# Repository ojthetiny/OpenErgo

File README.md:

# OpenErgo
 Open Source Alice Keyboard

 Use as a base for your own designs, renders or order as is (read important info at the bottom).

Details:

   - Alice layout
   - Supports OG Alice plate
   - Chonky external weight
   - 7.5 degree typing angle.
   - Flush USB-C connector built into the PCB
   - Skuf feet.
   - 3 Piece construction for no external screws (aside from weight)

Important Info (READ BEFORE ORDERING):

   - I do not offer any sort of warranty for this, nor can I be held liable if something goes wrong.
   - Renders are not fully representative of the final product
   - Please, PLEASE look over the design before you do anything with it, it's possible and very likely that there are some errors, I'm just a human.
   - Theoretically universal Alice pcb support (bottom side USB), though the connector is possibly slightly misaligned, still untested

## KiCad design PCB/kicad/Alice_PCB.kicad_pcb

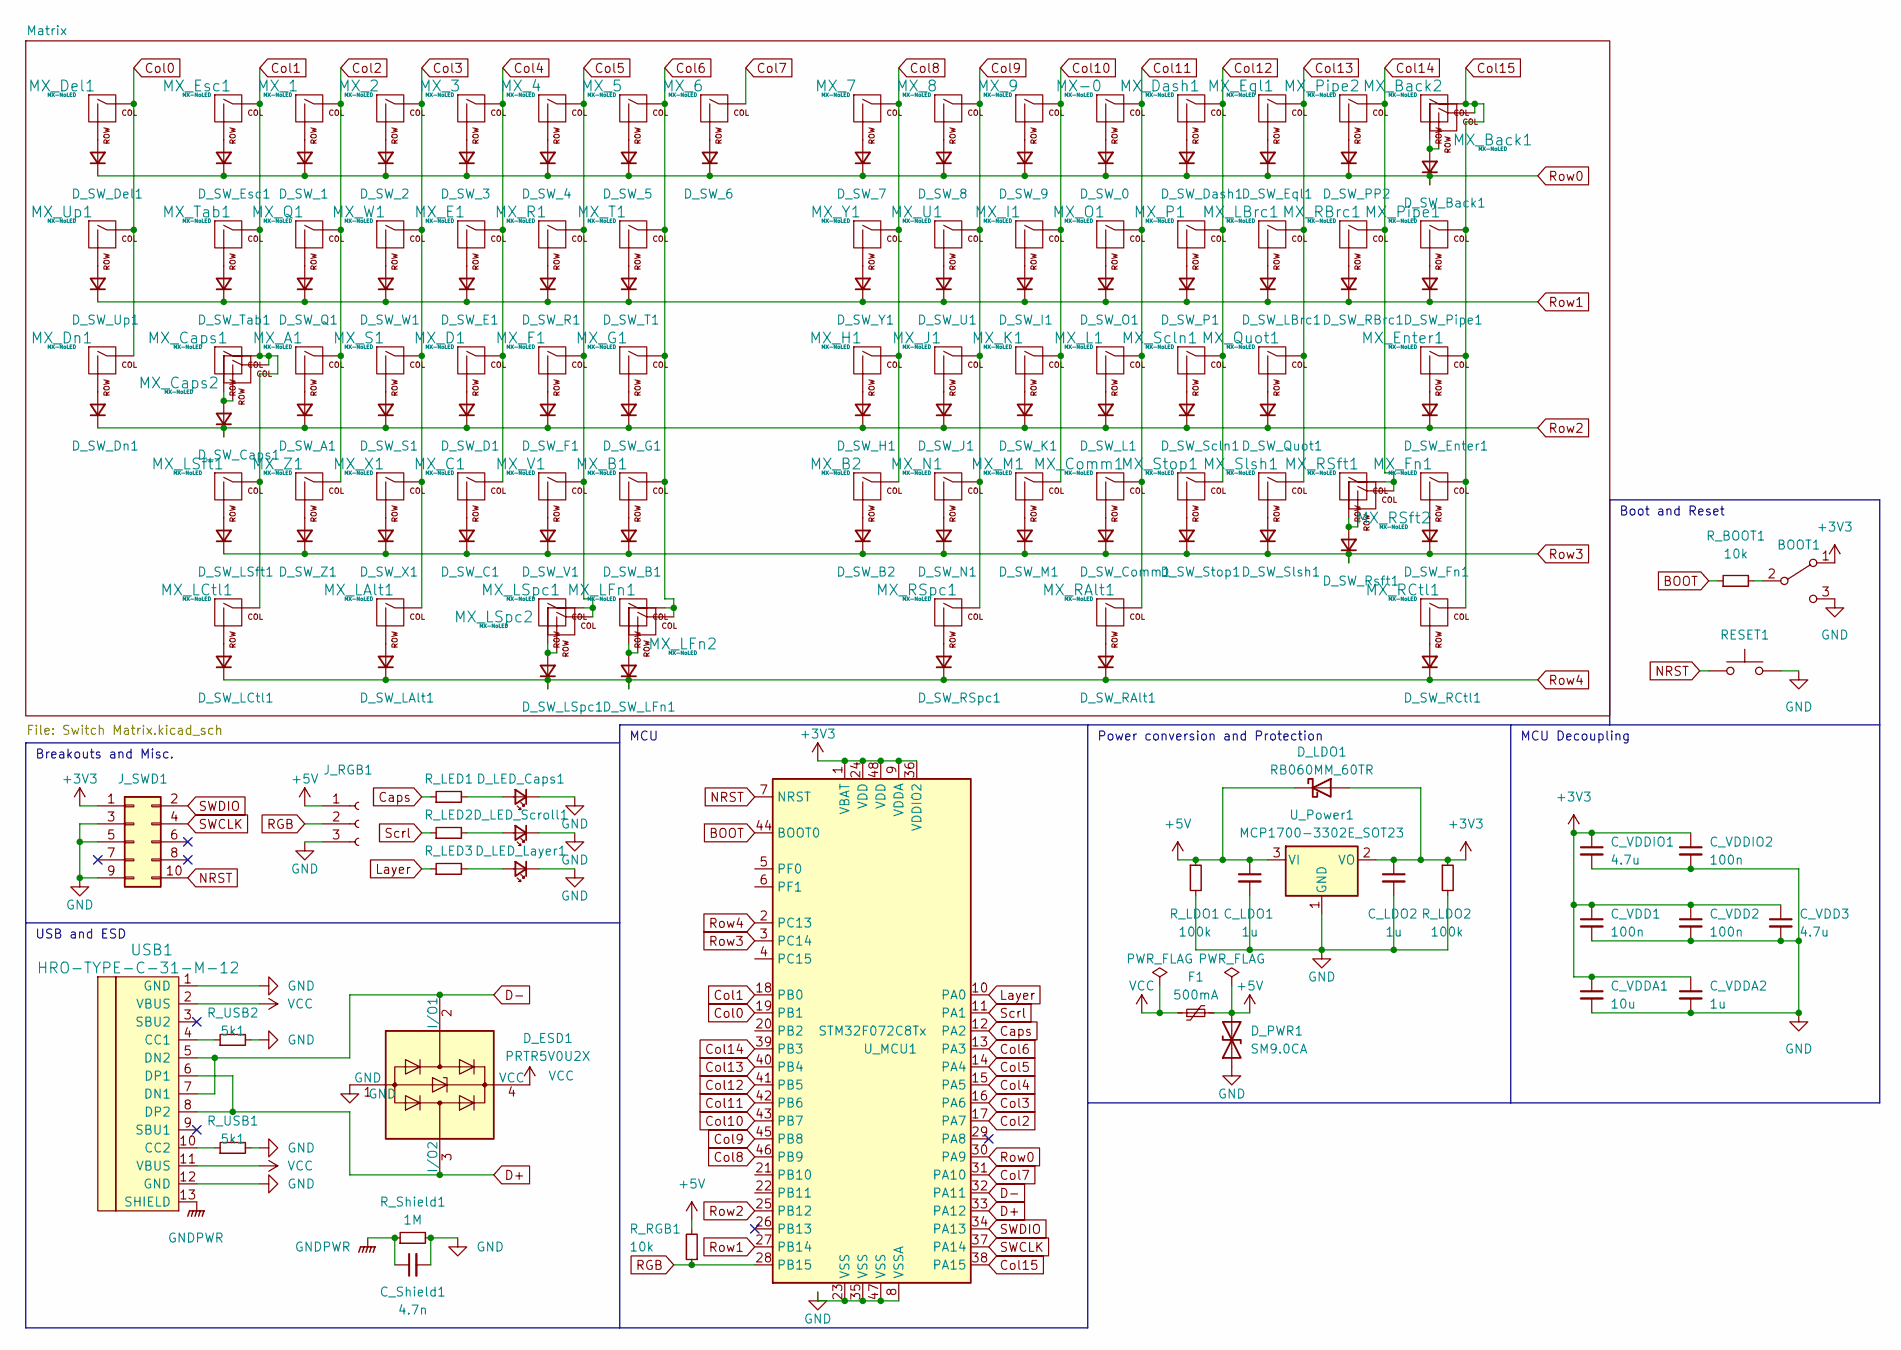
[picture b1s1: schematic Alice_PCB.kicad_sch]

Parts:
BOOT1: SW_SPDT; SW_SPDT_PCM12
C_LDO1, C_LDO2: 1u; C_0402_1005Metric
C_Shield1: 4.7n; C_0402_1005Metric
C_VDD1, C_VDD2: 100n; C_0402_1005Metric
C_VDD3: 4.7u; C_0402_1005Metric
C_VDDA1: 10u; C_0402_1005Metric
C_VDDA2: 1u; C_0402_1005Metric
C_VDDIO1: 4.7u; C_0402_1005Metric
C_VDDIO2: 100n; C_0402_1005Metric
D_ESD1: PRTR5V0U2X; SOT143B
D_LDO1: RB060MM_60TR; D_SOD-123
D_LED_Caps1: LED_Small; LED_3mm
D_LED_Layer1: LED_Small; LED_3mm
D_LED_Scroll1: LED_Small; LED_3mm
D_PWR1: SM9.0CA; D_SOD-123
D_SW_0, D_SW_1, D_SW_2, D_SW_3, D_SW_4, D_SW_5, D_SW_6, D_SW_7, D_SW_8, D_SW_9: D_Small; D_SOD-123
D_SW_A1: D_Small; D_SOD-123
D_SW_B1, D_SW_B2: D_Small; D_SOD-123
D_SW_Back1: D_Small; D_SOD-123
D_SW_C1: D_Small; D_SOD-123
D_SW_Caps1: D_Small; D_SOD-123
D_SW_Comm1: D_Small; D_SOD-123
D_SW_D1: D_Small; D_SOD-123
D_SW_Dash1: D_Small; D_SOD-123
D_SW_Del1: D_Small; D_SOD-123
D_SW_Dn1: D_Small; D_SOD-123
D_SW_E1: D_Small; D_SOD-123
D_SW_Enter1: D_Small; D_SOD-123
D_SW_Eql1: D_Small; D_SOD-123
D_SW_Esc1: D_Small; D_SOD-123
D_SW_F1: D_Small; D_SOD-123
D_SW_Fn1: D_Small; D_SOD-123
D_SW_G1: D_Small; D_SOD-123
D_SW_H1: D_Small; D_SOD-123
D_SW_I1: D_Small; D_SOD-123
D_SW_J1: D_Small; D_SOD-123
D_SW_K1: D_Small; D_SOD-123
D_SW_L1: D_Small; D_SOD-123
D_SW_LAlt1: D_Small; D_SOD-123
D_SW_LBrc1: D_Small; D_SOD-123
D_SW_LCtl1: D_Small; D_SOD-123
D_SW_LFn1: D_Small; D_SOD-123
D_SW_LSft1: D_Small; D_SOD-123
D_SW_LSpc1: D_Small; D_SOD-123
D_SW_M1: D_Small; D_SOD-123
D_SW_N1: D_Small; D_SOD-123
D_SW_O1: D_Small; D_SOD-123
D_SW_P1: D_Small; D_SOD-123
D_SW_PP2: D_Small; D_SOD-123
D_SW_Pipe1: D_Small; D_SOD-123
D_SW_Q1: D_Small; D_SOD-123
D_SW_Quot1: D_Small; D_SOD-123
D_SW_R1: D_Small; D_SOD-123
D_SW_RAlt1: D_Small; D_SOD-123
D_SW_RBrc1: D_Small; D_SOD-123
D_SW_RCtl1: D_Small; D_SOD-123
D_SW_RSpc1: D_Small; D_SOD-123
D_SW_Rsft1: D_Small; D_SOD-123
D_SW_S1: D_Small; D_SOD-123
D_SW_Scln1: D_Small; D_SOD-123
D_SW_Slsh1: D_Small; D_SOD-123
D_SW_Stop1: D_Small; D_SOD-123
D_SW_T1: D_Small; D_SOD-123
D_SW_Tab1: D_Small; D_SOD-123
D_SW_U1: D_Small; D_SOD-123
D_SW_Up1: D_Small; D_SOD-123
D_SW_V1: D_Small; D_SOD-123
D_SW_W1: D_Small; D_SOD-123
D_SW_X1: D_Small; D_SOD-123
D_SW_Y1: D_Small; D_SOD-123
D_SW_Z1: D_Small; D_SOD-123
F1: 500mA; Fuse_0805_2012Metric
J_RGB1: RGB; PinHeader_1x03_P2.54mm_Vertical
J_SWD1: SWD; PinHeader_2x05_P2.54mm_Vertical
MX-0: MX-NoLED; MX_1u_NoLED
MX_1, MX_2, MX_3, MX_4, MX_5, MX_6, MX_7, MX_8, MX_9: MX-NoLED; MX_1u_NoLED
MX_A1: MX-NoLED; MX_1u_NoLED
MX_B1, MX_B2: MX-NoLED; MX_1u_NoLED
MX_Back1: MX-NoLED; MX_2u_NoLED
MX_Back2: MX-NoLED; MX_1u_NoLED
MX_C1: MX-NoLED; MX_1u_NoLED
MX_Caps1: MX-NoLED; MX_1.75u_NoLED
MX_Caps2: MX-NoLED; MX_1.25u_NoLED
MX_Comm1: MX-NoLED; MX_1u_NoLED
MX_D1: MX-NoLED; MX_1u_NoLED
MX_Dash1: MX-NoLED; MX_1u_NoLED
MX_Del1: MX-NoLED; MX_1u_NoLED
MX_Dn1: MX-NoLED; MX_1u_NoLED
MX_E1: MX-NoLED; MX_1u_NoLED
MX_Enter1: MX-NoLED; MX_2.25u_ReversedStabilizers_NoLED
MX_Eql1: MX-NoLED; MX_1u_NoLED
MX_Esc1: MX-NoLED; MX_1u_NoLED
MX_F1: MX-NoLED; MX_1u_NoLED
MX_Fn1: MX-NoLED; MX_1u_NoLED
MX_G1: MX-NoLED; MX_1u_NoLED
MX_H1: MX-NoLED; MX_1u_NoLED
MX_I1: MX-NoLED; MX_1u_NoLED
MX_J1: MX-NoLED; MX_1u_NoLED
MX_K1: MX-NoLED; MX_1u_NoLED
MX_L1: MX-NoLED; MX_1u_NoLED
MX_LAlt1: MX-NoLED; MX_1.5u_NoLED
MX_LBrc1: MX-NoLED; MX_1u_NoLED
MX_LCtl1: MX-NoLED; MX_1.5u_NoLED
MX_LFn1: MX-NoLED; MX_1u_NoLED
MX_LFn2: MX-NoLED; MX_1.25u_NoLED
MX_LSft1: MX-NoLED; MX_2.25u_NoLED
MX_LSpc1: MX-NoLED; MX_2.25u_ReversedStabilizers_NoLED
MX_LSpc2: MX-NoLED; MX_2u_ReversedStabilizers_NoLED
MX_M1: MX-NoLED; MX_1u_NoLED
MX_N1: MX-NoLED; MX_1u_NoLED
MX_O1: MX-NoLED; MX_1u_NoLED
MX_P1: MX-NoLED; MX_1u_NoLED
MX_Pipe1: MX-NoLED; MX_1.5u_NoLED
MX_Pipe2: MX-NoLED; MX_1u_NoLED
MX_Q1: MX-NoLED; MX_1u_NoLED
MX_Quot1: MX-NoLED; MX_1u_NoLED
MX_R1: MX-NoLED; MX_1u_NoLED
MX_RAlt1: MX-NoLED; MX_1.5u_NoLED
MX_RBrc1: MX-NoLED; MX_1u_NoLED
MX_RCtl1: MX-NoLED; MX_1.5u_NoLED
MX_RSft1: MX-NoLED; MX_2.75u_NoLED
MX_RSft2: MX-NoLED; MX_1.75u_NoLED
MX_RSpc1: MX-NoLED; MX_2.75u_ReversedStabilizers_NoLED
MX_S1: MX-NoLED; MX_1u_NoLED
MX_Scln1: MX-NoLED; MX_1u_NoLED
MX_Slsh1: MX-NoLED; MX_1u_NoLED
MX_Stop1: MX-NoLED; MX_1u_NoLED
MX_T1: MX-NoLED; MX_1u_NoLED
MX_Tab1: MX-NoLED; MX_1.5u_NoLED
MX_U1: MX-NoLED; MX_1u_NoLED
MX_Up1: MX-NoLED; MX_1u_NoLED
MX_V1: MX-NoLED; MX_1u_NoLED
MX_W1: MX-NoLED; MX_1u_NoLED
MX_X1: MX-NoLED; MX_1u_NoLED
MX_Y1: MX-NoLED; MX_1u_NoLED
MX_Z1: MX-NoLED; MX_1u_NoLED
RESET1: SW_Push; SW_SPST_TL3342
R_BOOT1: 10k; R_0402_1005Metric
R_LDO1, R_LDO2: 100k; R_0402_1005Metric
R_LED1, R_LED2, R_LED3: R_Small; R_0402_1005Metric
R_RGB1: 10k; R_0402_1005Metric
R_Shield1: 1M; R_0402_1005Metric
R_USB1, R_USB2: 5k1; R_0402_1005Metric
USB1: HRO-TYPE-C-31-M-12; HRO-TYPE-C-31-M-12-Assembly
U_MCU1: STM32F072C8Tx; LQFP-48_7x7mm_P0.5mm
U_Power1: MCP1700-3302E_SOT23; SOT-23

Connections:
+3V3: BOOT1.1 (A), C_LDO2.1, C_VDD1.1, C_VDD2.1, C_VDD3.1, C_VDDA1.1, C_VDDA2.1, C_VDDIO1.1, C_VDDIO2.1, D_LDO1.2 (A), J_SWD1.1, R_LDO2.1, U_MCU1.1 (VBAT), U_MCU1.9 (VDDA), U_MCU1.24 (VDD), U_MCU1.36 (VDDIO2), U_MCU1.48 (VDD), U_Power1.2 (VO)
+5V: C_LDO1.1, D_LDO1.1 (K), D_PWR1.2 (A2), F1.2, J_RGB1.1, R_LDO1.1, R_RGB1.2, U_Power1.3 (VI)
BOOT: R_BOOT1.1, U_MCU1.44 (BOOT0)
Caps: R_LED1.1, U_MCU1.12 (PA2)
Col0: MX_Del1.1 (COL), MX_Dn1.1 (COL), MX_Up1.1 (COL), U_MCU1.19 (PB1)
Col1: MX_Caps1.1 (COL), MX_Caps2.1 (COL), MX_Esc1.1 (COL), MX_LCtl1.1 (COL), MX_LSft1.1 (COL), MX_Tab1.1 (COL), U_MCU1.18 (PB0)
Col2: MX_1.1 (COL), MX_A1.1 (COL), MX_Q1.1 (COL), MX_Z1.1 (COL), U_MCU1.17 (PA7)
Col3: MX_2.1 (COL), MX_LAlt1.1 (COL), MX_S1.1 (COL), MX_W1.1 (COL), MX_X1.1 (COL), U_MCU1.16 (PA6)
Col4: MX_3.1 (COL), MX_C1.1 (COL), MX_D1.1 (COL), MX_E1.1 (COL), U_MCU1.15 (PA5)
Col5: MX_4.1 (COL), MX_F1.1 (COL), MX_LSpc1.1 (COL), MX_LSpc2.1 (COL), MX_R1.1 (COL), MX_V1.1 (COL), U_MCU1.14 (PA4)
Col6: MX_5.1 (COL), MX_B1.1 (COL), MX_G1.1 (COL), MX_LFn1.1 (COL), MX_LFn2.1 (COL), MX_T1.1 (COL), U_MCU1.13 (PA3)
Col7: MX_6.1 (COL), U_MCU1.31 (PA10)
Col8: MX_7.1 (COL), MX_B2.1 (COL), MX_H1.1 (COL), MX_Y1.1 (COL), U_MCU1.46 (PB9)
Col9: MX_8.1 (COL), MX_J1.1 (COL), MX_N1.1 (COL), MX_RSpc1.1 (COL), MX_U1.1 (COL), U_MCU1.45 (PB8)
Col10: MX_9.1 (COL), MX_I1.1 (COL), MX_K1.1 (COL), MX_M1.1 (COL), U_MCU1.43 (PB7)
Col11: MX-0.1 (COL), MX_Comm1.1 (COL), MX_L1.1 (COL), MX_O1.1 (COL), MX_RAlt1.1 (COL), U_MCU1.42 (PB6)
Col12: MX_Dash1.1 (COL), MX_P1.1 (COL), MX_Scln1.1 (COL), MX_Stop1.1 (COL), U_MCU1.41 (PB5)
Col13: MX_Eql1.1 (COL), MX_LBrc1.1 (COL), MX_Quot1.1 (COL), MX_Slsh1.1 (COL), U_MCU1.40 (PB4)
Col14: MX_Pipe2.1 (COL), MX_RBrc1.1 (COL), MX_RSft1.1 (COL), MX_RSft2.1 (COL), U_MCU1.39 (PB3)
Col15: MX_Back1.1 (COL), MX_Back2.1 (COL), MX_Enter1.1 (COL), MX_Fn1.1 (COL), MX_Pipe1.1 (COL), MX_RCtl1.1 (COL), U_MCU1.38 (PA15)
D+: D_ESD1.3 (I/O2), USB1.6 (DP1), USB1.8 (DP2), U_MCU1.33 (PA12)
D-: D_ESD1.2 (I/O1), USB1.5 (DN2), USB1.7 (DN1), U_MCU1.32 (PA11)
GND: BOOT1.3 (C), C_LDO1.2, C_LDO2.2, C_Shield1.2, C_VDD1.2, C_VDD2.2, C_VDD3.2, C_VDDA1.2, C_VDDA2.2, C_VDDIO1.2, C_VDDIO2.2, D_ESD1.1 (GND), D_LED_Caps1.1 (K), D_LED_Layer1.1 (K), D_LED_Scroll1.1 (K), D_PWR1.1 (A1), J_RGB1.3, J_SWD1.3, J_SWD1.5, J_SWD1.9, RESET1.2, R_LDO1.2, R_LDO2.2, R_Shield1.2, R_USB1.2, R_USB2.2, USB1.1 (GND), USB1.12 (GND), U_MCU1.8 (VSSA), U_MCU1.23 (VSS), U_MCU1.35 (VSS), U_MCU1.47 (VSS), U_Power1.1 (GND)
GNDPWR: C_Shield1.1, R_Shield1.1, USB1.13 (SHIELD)
Layer: R_LED3.1, U_MCU1.10 (PA0)
NRST: J_SWD1.10, RESET1.1, U_MCU1.7 (NRST)
unnamed: D_LED_Layer1.2 (A), R_LED3.2
unnamed: D_SW_Back1.2 (A), MX_Back1.2 (ROW), MX_Back2.2 (ROW)
unnamed: D_SW_E1.2 (A), MX_E1.2 (ROW)
unnamed 29: D_SW_I1.2 (A), MX_I1.2 (ROW); also elsewhere on the board
unnamed: D_SW_LBrc1.2 (A), MX_LBrc1.2 (ROW)
unnamed: D_SW_O1.2 (A), MX_O1.2 (ROW)
unnamed: D_SW_P1.2 (A), MX_P1.2 (ROW)
unnamed: D_SW_Pipe1.2 (A), MX_Pipe1.2 (ROW)
unnamed: D_SW_Q1.2 (A), MX_Q1.2 (ROW)
unnamed: D_SW_R1.2 (A), MX_R1.2 (ROW)
unnamed: D_SW_RBrc1.2 (A), MX_RBrc1.2 (ROW)
unnamed: D_SW_T1.2 (A), MX_T1.2 (ROW)
unnamed: D_SW_Tab1.2 (A), MX_Tab1.2 (ROW)
unnamed: D_SW_U1.2 (A), MX_U1.2 (ROW)
unnamed: D_SW_Up1.2 (A), MX_Up1.2 (ROW)
unnamed: D_SW_W1.2 (A), MX_W1.2 (ROW)
unnamed: D_SW_Y1.2 (A), MX_Y1.2 (ROW)
unnamed: D_SW_0.2 (A), MX-0.2 (ROW)
unnamed: D_SW_1.2 (A), MX_1.2 (ROW)
unnamed: D_SW_2.2 (A), MX_2.2 (ROW)
unnamed: D_SW_3.2 (A), MX_3.2 (ROW)
unnamed: D_SW_4.2 (A), MX_4.2 (ROW)
unnamed: D_SW_5.2 (A), MX_5.2 (ROW)
unnamed: D_SW_6.2 (A), MX_6.2 (ROW)
unnamed: D_SW_7.2 (A), MX_7.2 (ROW)
unnamed: D_SW_8.2 (A), MX_8.2 (ROW)
unnamed: D_SW_9.2 (A), MX_9.2 (ROW)
unnamed: D_SW_A1.2 (A), MX_A1.2 (ROW)
unnamed: D_SW_B1.2 (A), MX_B1.2 (ROW)
unnamed: D_SW_B2.2 (A), MX_B2.2 (ROW)
unnamed: D_SW_C1.2 (A), MX_C1.2 (ROW)
unnamed: D_SW_Caps1.2 (A), MX_Caps1.2 (ROW), MX_Caps2.2 (ROW)
unnamed: D_SW_Comm1.2 (A), MX_Comm1.2 (ROW)
unnamed: D_SW_D1.2 (A), MX_D1.2 (ROW)
unnamed: D_SW_Dash1.2 (A), MX_Dash1.2 (ROW)
unnamed: D_SW_Del1.2 (A), MX_Del1.2 (ROW)
unnamed: D_SW_Dn1.2 (A), MX_Dn1.2 (ROW)
unnamed: D_SW_Enter1.2 (A), MX_Enter1.2 (ROW)
unnamed: D_SW_Eql1.2 (A), MX_Eql1.2 (ROW)
unnamed: D_SW_Esc1.2 (A), MX_Esc1.2 (ROW)
unnamed: D_SW_F1.2 (A), MX_F1.2 (ROW)
unnamed: D_SW_Fn1.2 (A), MX_Fn1.2 (ROW)
unnamed: D_SW_G1.2 (A), MX_G1.2 (ROW)
unnamed: D_SW_H1.2 (A), MX_H1.2 (ROW)
unnamed: D_SW_J1.2 (A), MX_J1.2 (ROW)
unnamed: D_SW_K1.2 (A), MX_K1.2 (ROW)
unnamed: D_SW_L1.2 (A), MX_L1.2 (ROW)
unnamed: D_SW_LAlt1.2 (A), MX_LAlt1.2 (ROW)
unnamed: D_SW_LCtl1.2 (A), MX_LCtl1.2 (ROW)
unnamed: D_SW_LFn1.2 (A), MX_LFn1.2 (ROW), MX_LFn2.2 (ROW)
unnamed: D_SW_LSft1.2 (A), MX_LSft1.2 (ROW)
unnamed: D_SW_LSpc1.2 (A), MX_LSpc1.2 (ROW), MX_LSpc2.2 (ROW)
unnamed: D_SW_M1.2 (A), MX_M1.2 (ROW)
unnamed: D_SW_N1.2 (A), MX_N1.2 (ROW)
unnamed: D_SW_PP2.2 (A), MX_Pipe2.2 (ROW)
unnamed: D_SW_Quot1.2 (A), MX_Quot1.2 (ROW)
unnamed: D_SW_RAlt1.2 (A), MX_RAlt1.2 (ROW)
unnamed: D_SW_RCtl1.2 (A), MX_RCtl1.2 (ROW)
unnamed: D_SW_Rsft1.2 (A), MX_RSft1.2 (ROW), MX_RSft2.2 (ROW)
unnamed: D_SW_RSpc1.2 (A), MX_RSpc1.2 (ROW)
unnamed: D_SW_S1.2 (A), MX_S1.2 (ROW)
unnamed: D_SW_Scln1.2 (A), MX_Scln1.2 (ROW)
unnamed: D_SW_Slsh1.2 (A), MX_Slsh1.2 (ROW)
unnamed: D_SW_Stop1.2 (A), MX_Stop1.2 (ROW)
unnamed: D_SW_V1.2 (A), MX_V1.2 (ROW)
unnamed: D_SW_X1.2 (A), MX_X1.2 (ROW)
unnamed: D_SW_Z1.2 (A), MX_Z1.2 (ROW)
unnamed: BOOT1.2 (B), R_BOOT1.2
unnamed: D_LED_Caps1.2 (A), R_LED1.2
unnamed: D_LED_Scroll1.2 (A), R_LED2.2
unnamed: R_USB2.1, USB1.4 (CC1)
unnamed: R_USB1.1, USB1.10 (CC2)
RGB: J_RGB1.2, R_RGB1.1, U_MCU1.28 (PB15)
Row0: D_SW_0.1 (K), D_SW_1.1 (K), D_SW_2.1 (K), D_SW_3.1 (K), D_SW_4.1 (K), D_SW_5.1 (K), D_SW_6.1 (K), D_SW_7.1 (K), D_SW_8.1 (K), D_SW_9.1 (K), D_SW_Back1.1 (K), D_SW_Dash1.1 (K), D_SW_Del1.1 (K), D_SW_Eql1.1 (K), D_SW_Esc1.1 (K), D_SW_PP2.1 (K), U_MCU1.30 (PA9)
Row1: D_SW_E1.1 (K), D_SW_I1.1 (K), D_SW_LBrc1.1 (K), D_SW_O1.1 (K), D_SW_P1.1 (K), D_SW_Pipe1.1 (K), D_SW_Q1.1 (K), D_SW_R1.1 (K), D_SW_RBrc1.1 (K), D_SW_T1.1 (K), D_SW_Tab1.1 (K), D_SW_U1.1 (K), D_SW_Up1.1 (K), D_SW_W1.1 (K), D_SW_Y1.1 (K), U_MCU1.27 (PB14); also elsewhere on the board
Row2: D_SW_A1.1 (K), D_SW_Caps1.1 (K), D_SW_D1.1 (K), D_SW_Dn1.1 (K), D_SW_Enter1.1 (K), D_SW_F1.1 (K), D_SW_G1.1 (K), D_SW_H1.1 (K), D_SW_J1.1 (K), D_SW_K1.1 (K), D_SW_L1.1 (K), D_SW_Quot1.1 (K), D_SW_S1.1 (K), D_SW_Scln1.1 (K), U_MCU1.25 (PB12)
Row3: D_SW_B1.1 (K), D_SW_B2.1 (K), D_SW_C1.1 (K), D_SW_Comm1.1 (K), D_SW_Fn1.1 (K), D_SW_LSft1.1 (K), D_SW_M1.1 (K), D_SW_N1.1 (K), D_SW_Rsft1.1 (K), D_SW_Slsh1.1 (K), D_SW_Stop1.1 (K), D_SW_V1.1 (K), D_SW_X1.1 (K), D_SW_Z1.1 (K), U_MCU1.3 (PC14)
Row4: D_SW_LAlt1.1 (K), D_SW_LCtl1.1 (K), D_SW_LFn1.1 (K), D_SW_LSpc1.1 (K), D_SW_RAlt1.1 (K), D_SW_RCtl1.1 (K), D_SW_RSpc1.1 (K), U_MCU1.2 (PC13)
SWCLK: J_SWD1.4, U_MCU1.37 (PA14)
SWDIO: J_SWD1.2, U_MCU1.34 (PA13)
Scrl: R_LED2.1, U_MCU1.11 (PA1)
VCC: D_ESD1.4 (VCC), F1.1, USB1.2 (VBUS), USB1.11 (VBUS)

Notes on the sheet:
USB and ESD
Power conversion and Protection
MCU
Boot and Reset
MCU Decoupling
Breakouts and Misc.

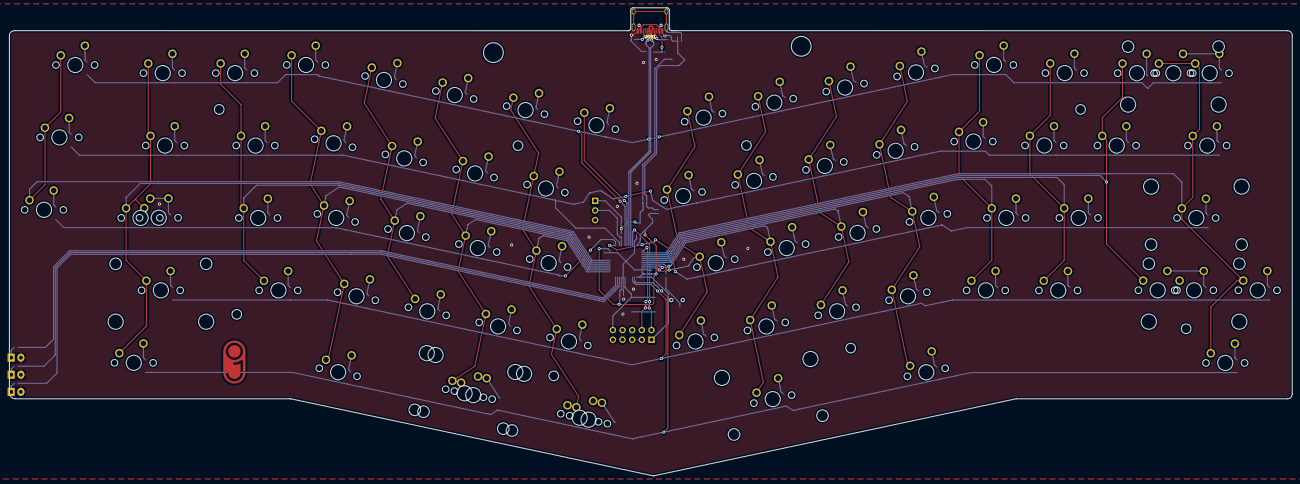
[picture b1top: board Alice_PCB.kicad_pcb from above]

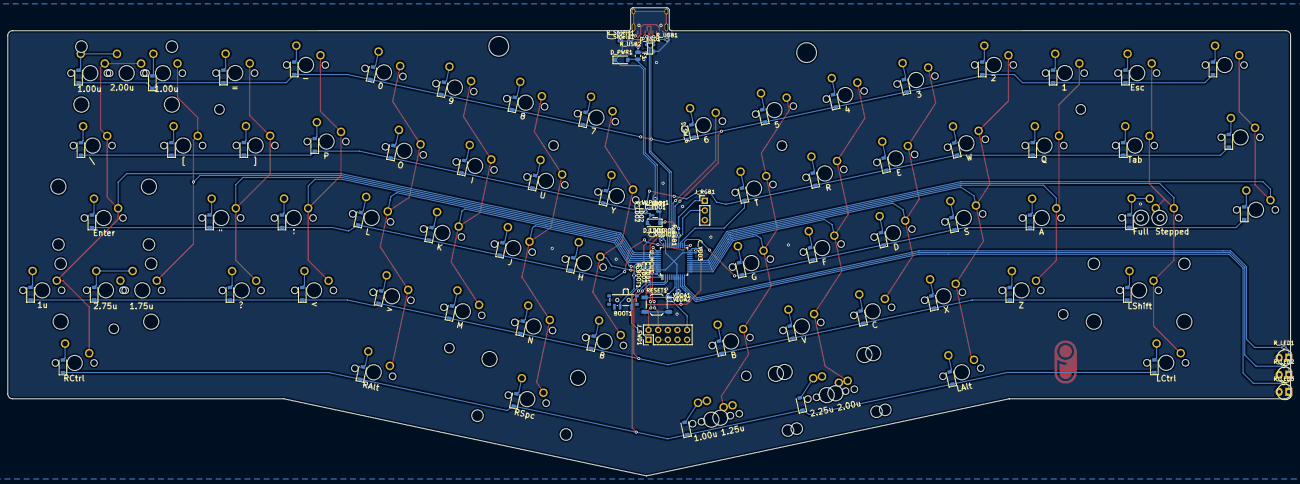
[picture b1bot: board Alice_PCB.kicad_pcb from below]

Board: 2 copper layers, 337.5 x 123.1 mm, 171 parts (99 on the bottom side), 108 nets.

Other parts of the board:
D_SW_Ie: D_Small; D_SOD-123

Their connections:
unnamed 29: D_SW_Ie.2 (A); also elsewhere on the board
Row1: D_SW_Ie.1 (K); also elsewhere on the board

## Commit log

2022-03-08 add image to readme
2022-03-08 Fixed couple typo's
2022-03-14 Fixed USB port positioning
    fixed the USB port position to fit other alice style cases, as well as changed USB from bottom to top mount
